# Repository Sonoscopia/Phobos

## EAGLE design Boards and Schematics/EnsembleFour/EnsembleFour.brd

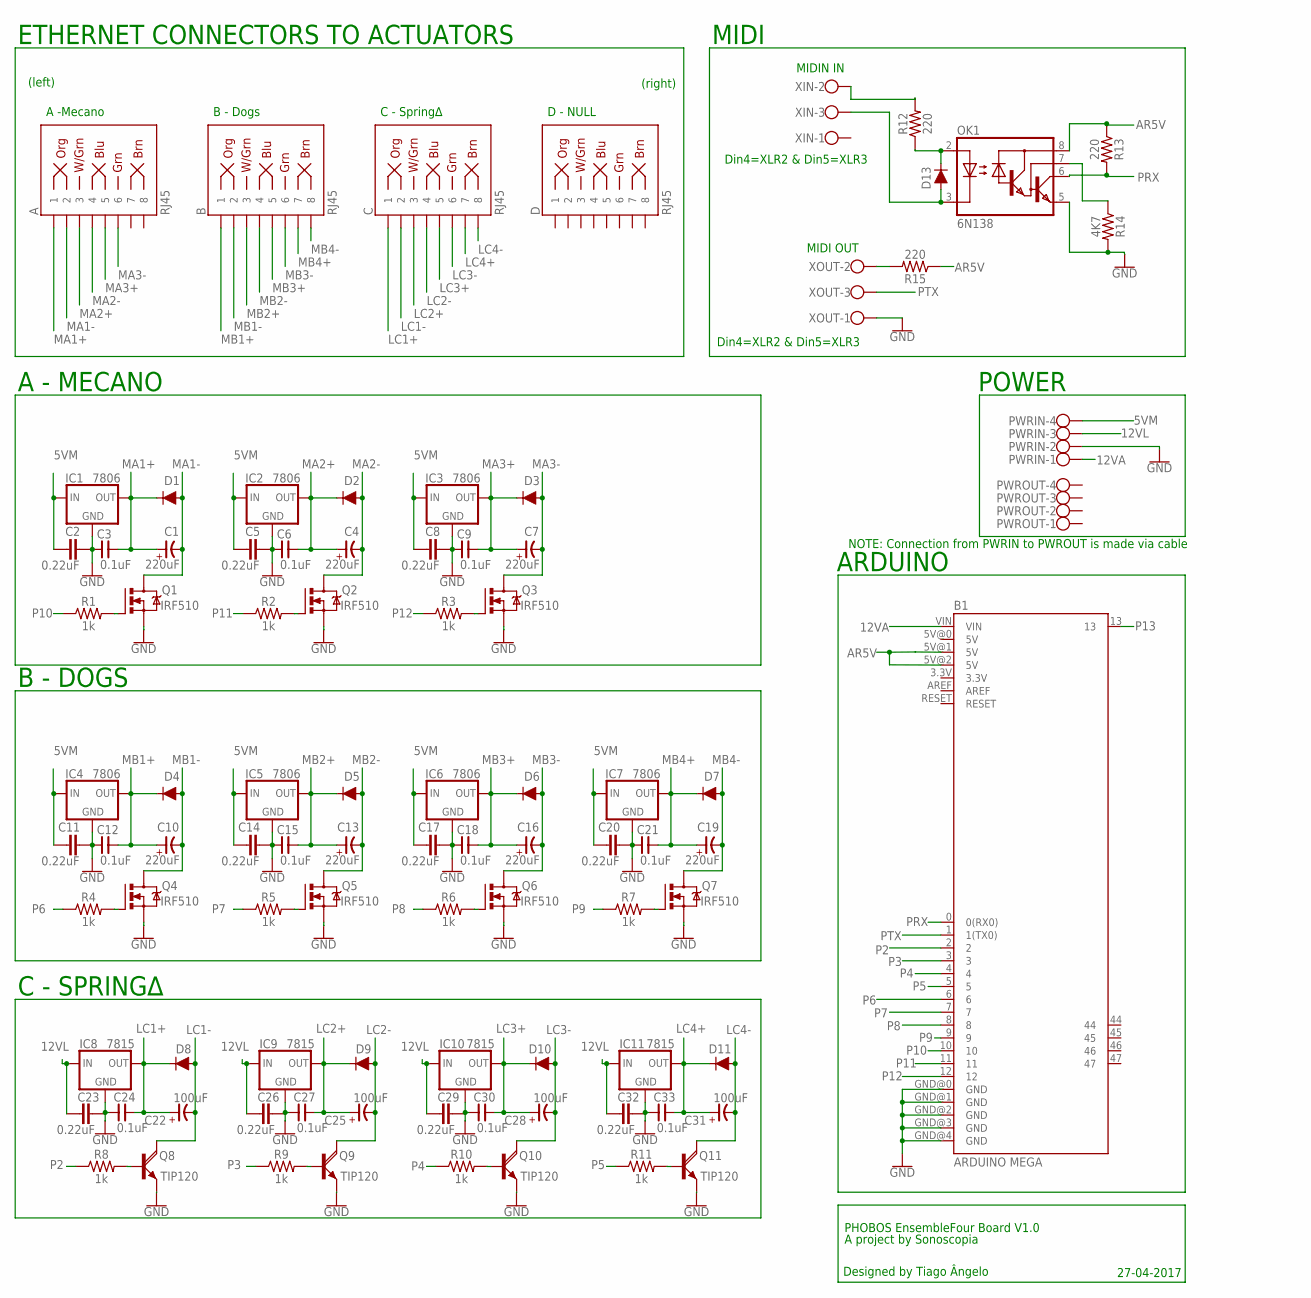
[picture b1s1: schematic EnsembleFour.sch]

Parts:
A: RJ45; RJ45-8
B: RJ45; RJ45-8
B1: ARDUINO MEGA; ARDUINO_MEGA
C: RJ45; RJ45-8
C1, C4, C7, C10, C13, C16, C19: 220uF; E-035X080
C2, C5, C8, C11, C14, C17, C20, C23, C26, C29, C32: 0.22uF; C5B3
C3, C6, C9, C12, C15, C18, C21, C24, C27, C30, C33: 0.1uF; C025-050X025
C22, C25, C28, C31: 100uF; E-020X050
D: RJ45; RJ45-8
D1, D2, D3, D4, D5, D6, D7, D8, D9, D10, D11: 1A/50V/1.1V; DIODE-1N4001-KIT
D13: 200mA/100V/1V; DIODE-1N4148
IC1, IC2, IC3, IC4, IC5, IC6, IC7: 7806; 78XXS
IC8, IC9, IC10, IC11: 7815; 78XXS
OK1: 6N138; DIL08
PWRIN: W237-4
PWROUT: W237-4
Q1, Q2, Q3, Q4, Q5, Q6, Q7: IRF510; TO220BV
Q8, Q9, Q10, Q11: TIP120; TO220AV
R1, R2, R3, R4, R5, R6, R7, R8, R9, R10, R11: 1k; AXIAL-0.1
R12, R13, R15: 220; AXIAL-0.3
R14: 4K7; AXIAL-0.3
XIN: W237-103
XOUT: W237-103

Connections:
5VM: C2.1, C5.1, C8.1, C11.1, C14.1, C17.1, C20.1, IC1.IN, IC2.IN, IC3.IN, IC4.IN, IC5.IN, IC6.IN, IC7.IN, PWRIN.4
12VA: B1.VIN, PWRIN.1
12VL: C23.1, C26.1, C29.1, C32.1, IC8.IN, IC9.IN, IC10.IN, IC11.IN, PWRIN.3
AR5V: B1.5V@1 (5V), B1.5V@2 (5V), OK1.8 (VCC), R13.P$1 (1), R15.P$1 (1)
GND: B1.GND@0 (GND), B1.GND@1 (GND), B1.GND@2 (GND), B1.GND@3 (GND), B1.GND@4 (GND), C2.2, C3.1, C5.2, C6.1, C8.2, C9.1, C11.2, C12.1, C14.2, C15.1, C17.2, C18.1, C20.2, C21.1, C23.2, C24.1, C26.2, C27.1, C29.2, C30.1, C32.2, C33.1, IC1.GND, IC2.GND, IC3.GND, IC4.GND, IC5.GND, IC6.GND, IC7.GND, IC8.GND, IC9.GND, IC10.GND, IC11.GND, OK1.5 (GND), PWRIN.2, Q1.S, Q2.S, Q3.S, Q4.S, Q5.S, Q6.S, Q7.S, Q8.E, Q9.E, Q10.E, Q11.E, R14.P$2 (2), XOUT.1
LC1+: C.1, C22.+, C24.2, D8.C, IC8.OUT
LC1-: C.2, C22.-, D8.A, Q8.C
LC2+: C.3, C25.+, C27.2, D9.C, IC9.OUT
LC2-: C.4, C25.-, D9.A, Q9.C
LC3+: C.5, C28.+, C30.2, D10.C, IC10.OUT
LC3-: C.6, C28.-, D10.A, Q10.C
LC4+: C.7, C31.+, C33.2, D11.C, IC11.OUT
LC4-: C.8, C31.-, D11.A, Q11.C
MA1+: A.1, C1.+, C3.2, D1.C, IC1.OUT
MA1-: A.2, C1.-, D1.A, Q1.D
MA2+: A.3, C4.+, C6.2, D2.C, IC2.OUT
MA2-: A.4, C4.-, D2.A, Q2.D
MA3+: A.5, C7.+, C9.2, D3.C, IC3.OUT
MA3-: A.6, C7.-, D3.A, Q3.D
MB1+: B.1, C10.+, C12.2, D4.C, IC4.OUT
MB1-: B.2, C10.-, D4.A, Q4.D
MB2+: B.3, C13.+, C15.2, D5.C, IC5.OUT
MB2-: B.4, C13.-, D5.A, Q5.D
MB3+: B.5, C16.+, C18.2, D6.C, IC6.OUT
MB3-: B.6, C16.-, D6.A, Q6.D
MB4+: B.7, C19.+, C21.2, D7.C, IC7.OUT
MB4-: B.8, C19.-, D7.A, Q7.D
unnamed: Q1.G, R1.P$2 (2)
unnamed: R15.P$2 (2), XOUT.2
unnamed: Q2.G, R2.P$2 (2)
unnamed: Q9.B, R9.P$2 (2)
unnamed: Q10.B, R10.P$2 (2)
unnamed: Q8.B, R8.P$2 (2)
unnamed: Q3.G, R3.P$2 (2)
unnamed: Q4.G, R4.P$2 (2)
unnamed: Q5.G, R5.P$2 (2)
unnamed: Q6.G, R6.P$2 (2)
unnamed: Q7.G, R7.P$2 (2)
unnamed: Q11.B, R11.P$2 (2)
unnamed: D13.A, OK1.3 (C), XIN.3
unnamed: D13.C, OK1.2 (A), R12.P$1 (1)
unnamed: R12.P$2 (2), XIN.2
unnamed: OK1.7 (VB), R14.P$1 (1)
P2: B1.2, R8.P$1 (1)
P3: B1.3, R9.P$1 (1)
P4: B1.4, R10.P$1 (1)
P5: B1.5, R11.P$1 (1)
P6: B1.6, R4.P$1 (1)
P7: B1.7, R5.P$1 (1)
P8: B1.8, R6.P$1 (1)
P9: B1.9, R7.P$1 (1)
P10: B1.10, R1.P$1 (1)
P11: B1.11, R2.P$1 (1)
P12: B1.12, R3.P$1 (1)
P13: B1.13
PRX: B1.0 (0(RX0)), OK1.6 (VO), R13.P$2 (2)
PTX: B1.1 (1(TX0)), XOUT.3

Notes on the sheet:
Din4=XLR2 & Din5=XLR3
MIDI OUT
MIDIN IN
POWER
MIDI
ARDUINO
(right)
(left)
ETHERNET CONNECTORS TO ACTUATORS
D - NULL
C - Spring∆
B - Dogs
A -Mecano
A - MECANO
C - SPRING∆
PHOBOS EnsembleFour Board V1.0
Designed by Tiago Ângelo
A project by Sonoscopia
27-04-2017
B - DOGS
NOTE: Connection from PWRIN to PWROUT is made via cable

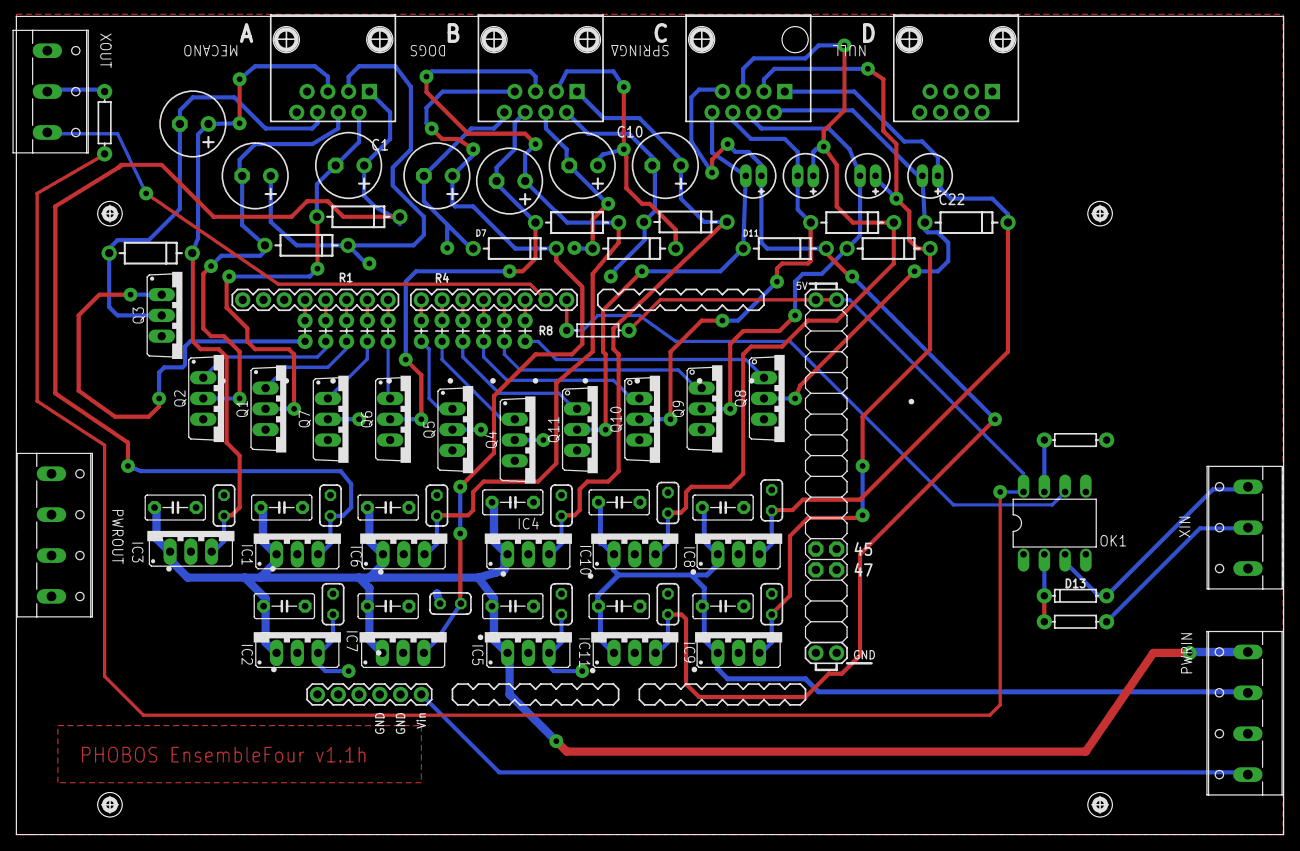
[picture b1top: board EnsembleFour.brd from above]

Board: 2 copper layers, 155.0 x 100.1 mm, 92 parts (0 on the bottom side), 56 nets.

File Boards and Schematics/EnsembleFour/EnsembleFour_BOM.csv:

Partlist exported from C:/Users/tiago/Documents/eagle/PHOBOS/EnsembleFour/EnsembleFour.sch at 05-05-2017 16:52

Qty Value         Device              Package          Parts                                              Description               MF                MPN     OC_FARNELL OC_NEWARK PROD_ID    SF_ID     VALUE        
2                 W237-103            W237-103         XIN, XOUT                                          WAGO SCREW CLAMP                            237-103 unknown    18M7116                                     
2                 W237-4              W237-4           PWRIN, PWROUT                                      WAGO SCREW CLAMP                                    unknown    unknown                                     
11  0.1uF         CNP-C025-050X025    C025-050X025     C3, C6, C9, C12, C15, C18, C21, C24, C27, C30, C33 NON-POLARIZED CAP                                                                                          
11  0.22uF        C5/3                C5B3             C2, C5, C8, C11, C14, C17, C20, C23, C26, C29, C32 CAPACITOR                                                                                                  
4   100uF         CP-E-020X050        E-020X050        C22, C25, C28, C31                                 POLARIZED CAP                                                                                              
11  1A/50V/1.1V   DIODE-KIT2          DIODE-1N4001-KIT D1, D2, D3, D4, D5, D6, D7, D8, D9, D10, D11       Diode                                                                    DIO-09176            1A/50V/1.1V  
11  1k            1KOHM-VERT-1/4W-1%  AXIAL-0.1        R1, R2, R3, R4, R5, R6, R7, R8, R9, R10, R11       1kO resistor                                                             RES-12182            1k           
1   200mA/100V/1V DIODE-1N4148        DIODE-1N4148     D13                                                Diode                                                                    DIO-08378            200mA/100V/1V
3   220           1KOHM-HORIZ-1/4W-5% AXIAL-0.3        R12, R13, R15                                      1kO resistor                                                             RES-08380            1k           
7   220uF         CP-E-035X080        E-035X080        C1, C4, C7, C10, C13, C16, C19                     POLARIZED CAP                                                                                              
1   4K7           1KOHM-HORIZ-1/4W-5% AXIAL-0.3        R14                                                1kO resistor                                                             RES-08380            1k           
1   6N138         6N138               DIL08            OK1                                                MOTOROLA OPTO COUPLER     VISHAY/TELEFUNKEN 6N138   9860150    35K5294                                     
7   7806          78XXS               78XXS            IC1, IC2, IC3, IC4, IC5, IC6, IC7                  VOLTAGE REGULATOR                                                                                          
4   7815          78XXS               78XXS            IC8, IC9, IC10, IC11                               VOLTAGE REGULATOR                                                                                          
1   ARDUINO MEGA  ARDUINO_MEGA_R3FULL ARDUINO_MEGA     B1                                                 Arduino Mega R3                                                                                            
7   IRF510        IRF520              TO220BV          Q1, Q2, Q3, Q4, Q5, Q6, Q7                         HEXFET Power MOSFET                                                                                        
4   RJ45          RJ45-8              RJ45-8           A, B, C, D                                         RJ45 Jack - 8 pin                                                        CONN-08506 PRT-00643 RJ45         
4   TIP120        TIP120V             TO220AV          Q8, Q9, Q10, Q11                                   NPN DARLINGTON TRANSISTOR

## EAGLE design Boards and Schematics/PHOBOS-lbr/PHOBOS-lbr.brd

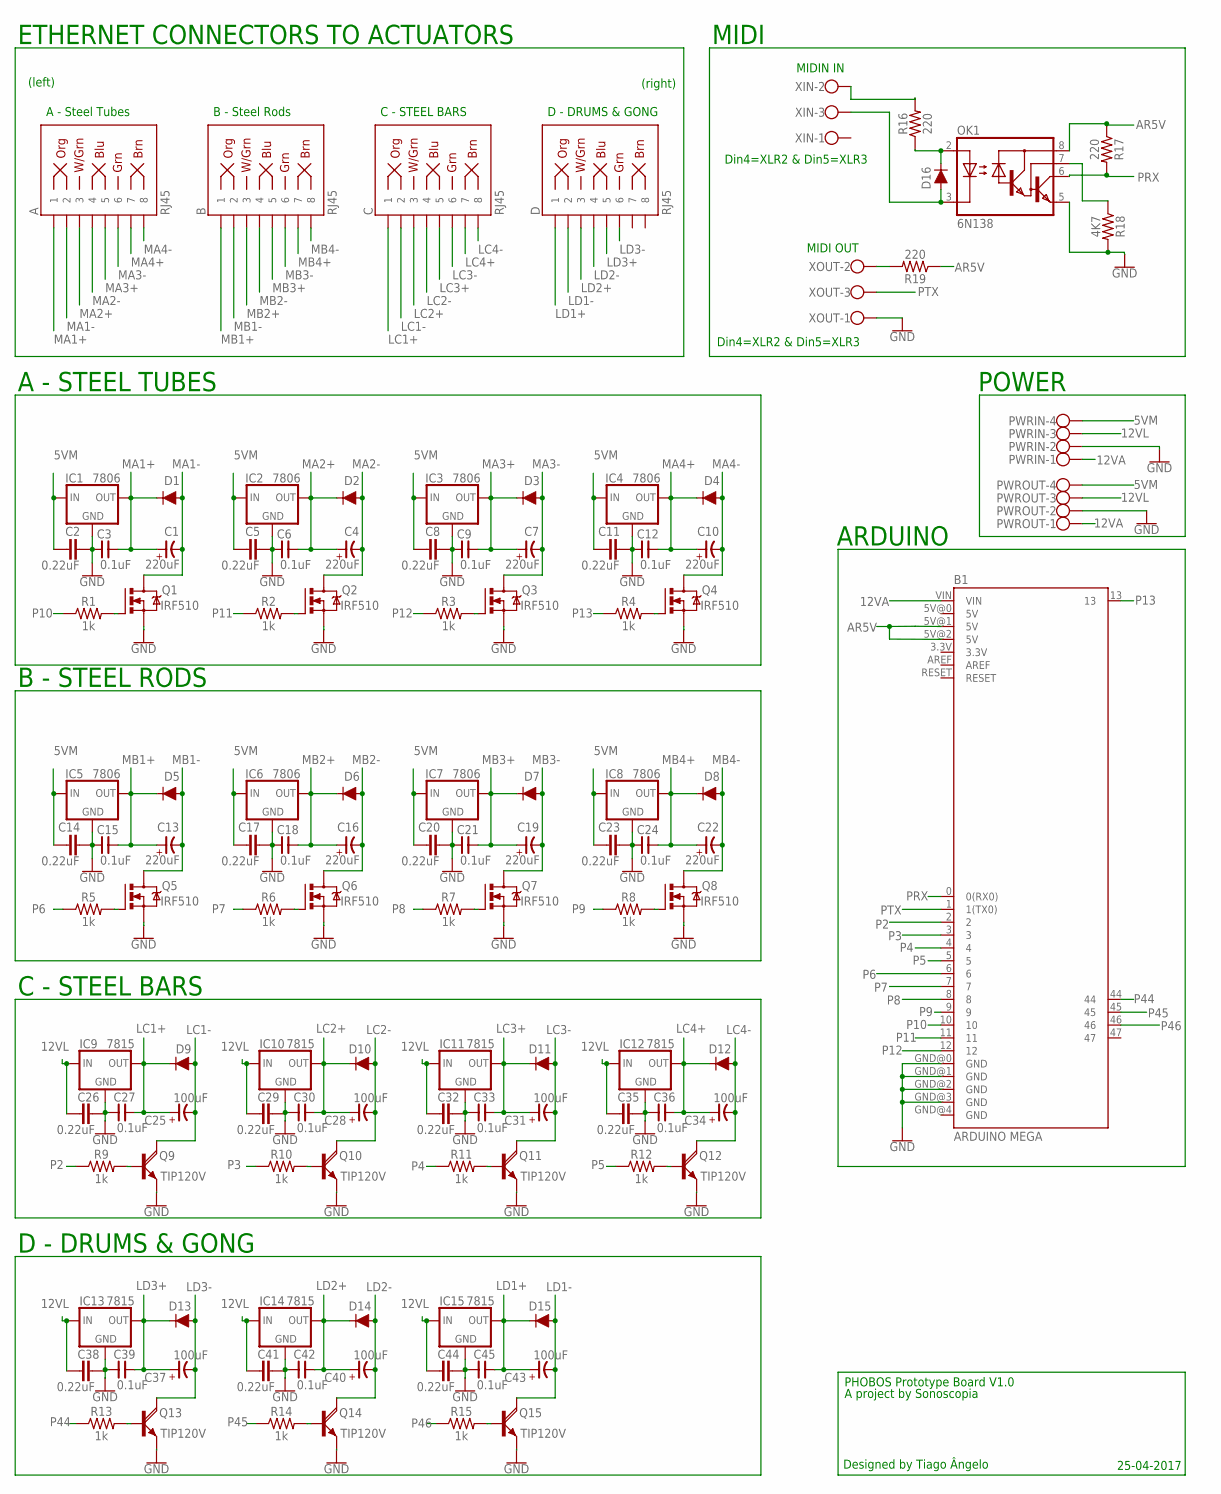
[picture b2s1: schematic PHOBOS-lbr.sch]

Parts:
A: RJ45; RJ45-8
B: RJ45; RJ45-8
B1: ARDUINO MEGA; ARDUINO_MEGA
C: RJ45; RJ45-8
C1, C4, C7, C10, C13, C16, C19, C22: 220uF; E-035X080
C2, C5, C8, C11, C14, C17, C20, C23, C26, C29, C32, C35, C38, C41, C44: 0.22uF; C5B3
C3, C6, C9, C12, C15, C18, C21, C24, C27, C30, C33, C36, C39, C42, C45: 0.1uF; C025-050X025
C25, C28, C31, C34, C37, C40, C43: 100uF; E-020X050
D: RJ45; RJ45-8
D1, D2, D3, D4, D5, D6, D7, D8, D9, D10, D11, D12, D13, D14, D15: 1A/50V/1.1V; DIODE-1N4001-KIT
D16: 200mA/100V/1V; DIODE-1N4148
IC1, IC2, IC3, IC4, IC5, IC6, IC7, IC8: 7806; 78XXS
IC9, IC10, IC11, IC12, IC13, IC14, IC15: 7815; 78XXS
OK1: 6N138; DIL08
PWRIN: W237-4
PWROUT: W237-4
Q1, Q2, Q3, Q4, Q5, Q6, Q7, Q8: IRF510; TO220BV
Q9, Q10, Q11, Q12, Q13, Q14, Q15: TIP120V; TO220AV
R1, R2, R3, R4, R5, R6, R7, R8, R9, R10, R11, R12, R13, R14, R15: 1k; AXIAL-0.1
R16, R17, R19: 220; AXIAL-0.3
R18: 4K7; AXIAL-0.3
XIN: W237-103
XOUT: W237-103

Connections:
5VM: C2.1, C5.1, C8.1, C11.1, C14.1, C17.1, C20.1, C23.1, IC1.IN, IC2.IN, IC3.IN, IC4.IN, IC5.IN, IC6.IN, IC7.IN, IC8.IN, PWRIN.4, PWROUT.4
12VA: B1.VIN, PWRIN.1, PWROUT.1
12VL: C26.1, C29.1, C32.1, C35.1, C38.1, C41.1, C44.1, IC9.IN, IC10.IN, IC11.IN, IC12.IN, IC13.IN, IC14.IN, IC15.IN, PWRIN.3, PWROUT.3
AR5V: B1.5V@1 (5V), B1.5V@2 (5V), OK1.8 (VCC), R17.P$1 (1), R19.P$1 (1)
GND: B1.GND@0 (GND), B1.GND@1 (GND), B1.GND@2 (GND), B1.GND@3 (GND), C2.2, C3.1, C5.2, C6.1, C8.2, C9.1, C11.2, C12.1, C14.2, C15.1, C17.2, C18.1, C20.2, C21.1, C23.2, C24.1, C26.2, C27.1, C29.2, C30.1, C32.2, C33.1, C35.2, C36.1, C38.2, C39.1, C41.2, C42.1, C44.2, C45.1, IC1.GND, IC2.GND, IC3.GND, IC4.GND, IC5.GND, IC6.GND, IC7.GND, IC8.GND, IC9.GND, IC10.GND, IC11.GND, IC12.GND, IC13.GND, IC14.GND, IC15.GND, OK1.5 (GND), PWRIN.2, PWROUT.2, Q1.S, Q2.S, Q3.S, Q4.S, Q5.S, Q6.S, Q7.S, Q8.S, Q9.E, Q10.E, Q11.E, Q12.E, Q13.E, Q14.E, Q15.E, R18.P$2 (2), XOUT.1
LC1+: C.1, C25.+, C27.2, D9.C, IC9.OUT
LC1-: C.2, C25.-, D9.A, Q9.C
LC2+: C.3, C28.+, C30.2, D10.C, IC10.OUT
LC2-: C.4, C28.-, D10.A, Q10.C
LC3+: C.5, C31.+, C33.2, D11.C, IC11.OUT
LC3-: C.6, C31.-, D11.A, Q11.C
LC4+: C.7, C34.+, C36.2, D12.C, IC12.OUT
LC4-: C.8, C34.-, D12.A, Q12.C
LD1+: C43.+, C45.2, D.1, D15.C, IC15.OUT
LD1-: C43.-, D.2, D15.A, Q15.C
LD2+: C40.+, C42.2, D.3, D14.C, IC14.OUT
LD2-: C40.-, D.4, D14.A, Q14.C
LD3+: C37.+, C39.2, D.5, D13.C, IC13.OUT
LD3-: C37.-, D.6, D13.A, Q13.C
MA1+: A.1, C1.+, C3.2, D1.C, IC1.OUT
MA1-: A.2, C1.-, D1.A, Q1.D
MA2+: A.3, C4.+, C6.2, D2.C, IC2.OUT
MA2-: A.4, C4.-, D2.A, Q2.D
MA3+: A.5, C7.+, C9.2, D3.C, IC3.OUT
MA3-: A.6, C7.-, D3.A, Q3.D
MA4+: A.7, C10.+, C12.2, D4.C, IC4.OUT
MA4-: A.8, C10.-, D4.A, Q4.D
MB1+: B.1, C13.+, C15.2, D5.C, IC5.OUT
MB1-: B.2, C13.-, D5.A, Q5.D
MB2+: B.3, C16.+, C18.2, D6.C, IC6.OUT
MB2-: B.4, C16.-, D6.A, Q6.D
MB3+: B.5, C19.+, C21.2, D7.C, IC7.OUT
MB3-: B.6, C19.-, D7.A, Q7.D
MB4+: B.7, C22.+, C24.2, D8.C, IC8.OUT
MB4-: B.8, C22.-, D8.A, Q8.D
unnamed: Q1.G, R1.P$2 (2)
unnamed: R19.P$2 (2), XOUT.2
unnamed: Q2.G, R2.P$2 (2)
unnamed: Q10.B, R10.P$2 (2)
unnamed: Q11.B, R11.P$2 (2)
unnamed: Q9.B, R9.P$2 (2)
unnamed: Q3.G, R3.P$2 (2)
unnamed: Q4.G, R4.P$2 (2)
unnamed: Q5.G, R5.P$2 (2)
unnamed: Q6.G, R6.P$2 (2)
unnamed: Q7.G, R7.P$2 (2)
unnamed: Q8.G, R8.P$2 (2)
unnamed: Q12.B, R12.P$2 (2)
unnamed: Q13.B, R13.P$2 (2)
unnamed: Q14.B, R14.P$2 (2)
unnamed: D16.A, OK1.3 (C), XIN.3
unnamed: D16.C, OK1.2 (A), R16.P$1 (1)
unnamed: R16.P$2 (2), XIN.2
unnamed: Q15.B, R15.P$2 (2)
unnamed: OK1.7 (VB), R18.P$1 (1)
P2: B1.2, R9.P$1 (1)
P3: B1.3, R10.P$1 (1)
P4: B1.4, R11.P$1 (1)
P5: B1.5, R12.P$1 (1)
P6: B1.6, R5.P$1 (1)
P7: B1.7, R6.P$1 (1)
P8: B1.8, R7.P$1 (1)
P9: B1.9, R8.P$1 (1)
P10: B1.10, R1.P$1 (1)
P11: B1.11, R2.P$1 (1)
P12: B1.12, R3.P$1 (1)
P13: B1.13, R4.P$1 (1)
P44: B1.44, R13.P$1 (1)
P45: B1.45, R14.P$1 (1)
P46: B1.46, R15.P$1 (1)
PRX: B1.0 (0(RX0)), OK1.6 (VO), R17.P$2 (2)
PTX: B1.1 (1(TX0)), XOUT.3

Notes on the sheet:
Din4=XLR2 & Din5=XLR3
MIDI OUT
MIDIN IN
POWER
MIDI
ARDUINO
(right)
(left)
ETHERNET CONNECTORS TO ACTUATORS
D - DRUMS & GONG
C - STEEL BARS
B - Steel Rods
A - Steel Tubes
A - STEEL TUBES
PHOBOS Prototype Board V1.0
Designed by Tiago Ângelo
A project by Sonoscopia
25-04-2017
B - STEEL RODS

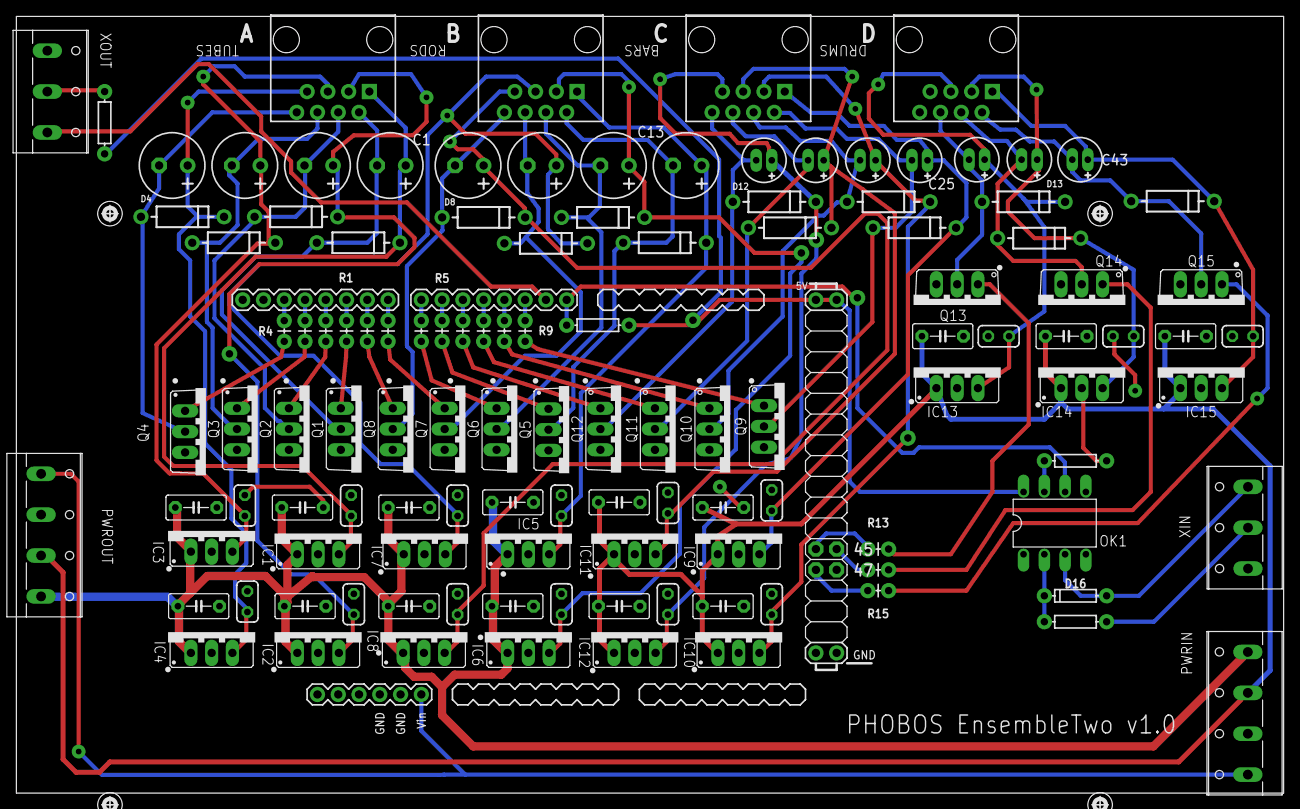
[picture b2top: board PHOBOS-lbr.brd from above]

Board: 2 copper layers, 155.0 x 95.0 mm, 120 parts (0 on the bottom side), 72 nets.

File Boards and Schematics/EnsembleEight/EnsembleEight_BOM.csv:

Partlist exported from C:/Users/tiago/Documents/eagle/PHOBOS/EnsembleEight/EnsembleEight.sch at 05-05-2017 16:57

Qty Value         Device                  Package              Parts                                    Description           MF                MPN     OC_FARNELL OC_NEWARK PROD_ID    SF_ID     VALUE        
2                 W237-103                W237-103             XIN, XOUT                                WAGO SCREW CLAMP                        237-103 unknown    18M7116                                     
2                 W237-4                  W237-4               PWRIN, PWROUT                            WAGO SCREW CLAMP                                unknown    unknown                                     
9   0.1uF         CNP-C025-050X025        C025-050X025         C3, C6, C9, C12, C15, C18, C20, C22, C24 NON-POLARIZED CAP                                                                                      
9   0.22uF        C5/3                    C5B3                 C2, C5, C8, C11, C14, C17, C19, C21, C23 CAPACITOR                                                                                              
3   100uF         CAP-MASTER_CP-E-020X050 CAP-MASTER_E-020X050 C10, C13, C16                            POLARIZED CAP                                                                                          
6   1A/50V/1.1V   DIODE-KIT2              DIODE-1N4001-KIT     D1, D2, D3, D4, D5, D6                   Diode                                                                DIO-09176            1A/50V/1.1V  
6   1k            1KOHM-VERT-1/4W-1%      AXIAL-0.1            R1, R2, R3, R4, R5, R6                   1kO resistor                                                         RES-12182            1k           
1   200mA/100V/1V DIODE-1N4148            DIODE-1N4148         D7                                       Diode                                                                DIO-08378            200mA/100V/1V
3   220           1KOHM-HORIZ-1/4W-5%     AXIAL-0.3            R7, R8, R10                              1kO resistor                                                         RES-08380            1k           
3   220uF         CP-E-035X080            E-035X080            C1, C4, C7                               POLARIZED CAP                                                                                          
1   4K7           1KOHM-HORIZ-1/4W-5%     AXIAL-0.3            R9                                       1kO resistor                                                         RES-08380            1k           
1   6N138         6N138                   DIL08                OK1                                      MOTOROLA OPTO COUPLER VISHAY/TELEFUNKEN 6N138   9860150    35K5294                                     
6   7806          78XXS                   78XXS                IC1, IC2, IC3, IC7, IC8, IC9             VOLTAGE REGULATOR                                                                                      
3   7815          78XXS                   78XXS                IC4, IC5, IC6                            VOLTAGE REGULATOR                                                                                      
1   ARDUINO MEGA  ARDUINO_MEGA_R3FULL     ARDUINO_MEGA         B1                                       Arduino Mega R3                                                                                        
6   IRF510        IRF520                  TO220BV              Q1, Q2, Q3, Q4, Q5, Q6                   HEXFET Power MOSFET                                                                                    
4   RJ45          RJ45-8                  RJ45-8               A, B, C, D                               RJ45 Jack - 8 pin                                                    CONN-08506 PRT-00643 RJ45

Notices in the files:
parts and their libraries:
SparkFun-Connectors: Licensing: Creative Commons ShareAlike 4.0 International - https://creativecommons.org/licenses/by-sa/4.0
